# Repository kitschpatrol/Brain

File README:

THIS IS THE SOFTWARE SERIAL BRANCH
==================================
Note, this branch is intended for use with the NewSoftSerial library. (The core SoftwareSerial library doesn't cut it, because it's missing certain function calls.)

Grab and install the NewSoftSerial library here: http://arduiniana.org/libraries/NewSoftSerial/

Eventually, changes to the Arduino core should eliminate the need for separate branches. (e.g. there should be a generic "Serial" object from which both the hardware and software varieties can inherit.)

If you want to use your hardware serial pins (0 and 1, usually), then use the Master branch of this library instead.

LIBRARY OVERVIEW
================
Brain is an Arduino Library for parsing data from Neurosky-based EEG headsets. Tested units include the Star Wars Force Trainer and Mattel MindFlex.

It's designed to make it simple to send out an ASCII string of comma-separated values over serial, or to access processed brain wave information directly in your Arduino sketch. See the examples for code demonstrating each use case.

Instructions for the hardware-end of this hack are available here: http://ericmika.com/itp/brain-hack

The .getCSV() function returns a string (well, char*) listing the most recent brain data, in the following format:
"signal strength, attention, meditation, delta, theta, low alpha, high alpha, low beta, high beta, low gamma, high gamma"

Signal strength ranges from 0 - 200. Counterintuitively, 0 means the unit has connected successfully, and 200 means there is no signal.

The attention and meditation values both run from 0 - 100. Intuitively, higher numbers represent more attention or meditation.

The EEG power values — delta, theta, etc... - are a heavily filtered representation of the relative activity in different brain wavelengths. These values can not be mapped directly to physical values (e.g. volts), but are still of use when considered over time or relative to each other.

INSTALLATION
============
Decompress the zip and drag "Brain" folder to Arduino's "libraries" folder inside your sketch folder. (On the Mac, this is ~/Documents/Arduino by default. You may need to create this folder if it does not exist.) Restart the Arduino environment.

FUNCTION OVERVIEW
=================
Brain(HardwareSerial &_brainSerial) // Instantiates the brain library on a hardware serial port.

boolean update();          // Call this in your main loop to read data from the headset. Returns true if there is a 
fresh packet.

char* readErrors();          // Character string containing the most recent errors. Worth printing this out over serial 
if you're having trouble.

char* readCSV();          // Character string with all of the latest brain values in a comma-delimited format. Intended 
to be printed over serial. The data is in this order: "signal strength, attention, meditation, delta, theta, low alpha, 
high alpha, low beta, high beta, low gamma, high gamma"

byte readSignalQuality();        // Returns the latest signal quality reading. 200 is high, 0 is no signal. This (and 
the remainder of the functions) are mainly intended for use when you want the Arduino to use the brain data internally. 
(Saves you the hassle / memory expenditure of parsing the CSV.)

byte readAttention();        // Returns the NeuroSky "eSense" attention value.

byte readMeditation();        // Returns the NeuroSky "eSense" meditation value.

unsigned long* readPowerArray();  // Returns an array of the eight power-band (FFT) values, in the same order as the 
CSV.

unsigned long readDelta();      // Returns the delta (1-3Hz) power value, often associated with sleep.

unsigned long readTheta();      // Returns the theta (4-7Hz) power value, associated with a relaxed, meditative state.

unsigned long readLowAlpha();    // Returns the low alpha (8-9Hz) power value, higher when eyes are closed or you're 
relaxed/

unsigned long readHighAlpha();    // Returns the high alpha (10-12Hz) power value.

unsigned long readLowBeta();     // Retursn the low beta (13-17Hz) power value, higher when you're alert and focused.

unsigned long readHighBeta();    // Returns the high beta (18-30Hz) power value.

unsigned long readLowGamma();    // Returns the low gamma (31-40Hz) power value, associated with multi-sensory 
processing.

unsigned long readMidGamma();    // Returns the high gamma (41-50Hz) power value.

MINUTIAE
========
Note that the connection to the Neurosky headset is half-duplex — it will use up the RX pin on your Arduino, but you will still be able to send data back to a PC via USB. (Although in this case you won't be able to send data to the Arduino from the PC.)

You may wish to read brain data over a software serial connection instead of the Arduino's hardware serial (this frees up the hardware serial for full-duplex operation). I've tested the library with the Software Serial library distributed with the Arduino environment, and also with the excellent NewSoftSerial library (http://arduiniana.org/libraries/NewSoftSerial), it works fine with both. HOWEVER, switching from the default hardware serial to software serial requires modification of the brain library. I'm looking for a more flexible solution, but for now feel free to contact me if you need help reconfiguring the library to work with software serial.

The MindFlex provides access to more brain data than the Force Trainer — in addition to the signal strength, attention and meditation values, the MindFlex gives access to 8 bands of EEG power data.

Brain data comes in quite slowly... expect a fresh packet every second or so.

CONTACT
========
Eric Mika
ermika@gmail.com
http://ericmika.com/itp

COLOPHON
========
Created by Eric Mika at NYU ITP in the spring of 2010.

My thanks to Tom Igoe for his assistance during development. Thanks also to my collaborators Sofy Yuditskaya and Arturo Vidich.

LICENSE
=======
Copyright Eric Mika, 2010
Licensed under the GNU Lesser General Public License.

This program is free software: you can redistribute it and/or modify it under the terms of the GNU Lesser General Public License as published by the Free Software Foundation, either version 3 of the License, or (at your option) any later version.

This program is distributed in the hope that it will be useful, but WITHOUT ANY WARRANTY; without even the implied warranty of MERCHANTABILITY or FITNESS FOR A PARTICULAR PURPOSE. See the GNU General Public License for more details.

You should have received a copy of the GNU Lesser General Public License along with this program. If not, see http://www.gnu.org/licenses/.

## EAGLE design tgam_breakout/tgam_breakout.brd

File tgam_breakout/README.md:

TGAM Breakout
=============

For Neurosky ThinkGear ASIC Module. breaks out the 2.0mm pitch pins from the
TGAM board to coax and 2.54mm pitch connectors. Has electrode pads too.

Seeed did produce a batch of these for me, they did ask me to doublecheck since this does not pass the DRU but the result was fine. Remember to order in ENIG finish.

## BOM

  - 1 TGAM: http://www.seeedstudio.com/depot/thinkgear-am-brainwave-sensor-p-1441.html?cPath=25_29
  - 1 6 contact pin header 2.0mm: http://www.digikey.fi/product-detail/en/M22-2020305/952-2133-ND/3728097
  - 1 5 contact pin header 2.0mm: http://www.digikey.fi/product-detail/en/M22-2010505/952-2276-ND/3728240
  - 3 UMC cables: http://www.digikey.fi/product-detail/en/2015357-4/A36229-ND/1249193
  - 6 UMC connectors: http://www.digikey.fi/product-detail/en/0734120114/WM3894CT-ND/2421931

Instead of the expensive coax cable and connectors you can use shielded
audio cable and solder that directly on the board, the signal wire goes
on the coax middle (the trace is easy to identify) and shield goes to
either of the two pads of the coax connector shields.

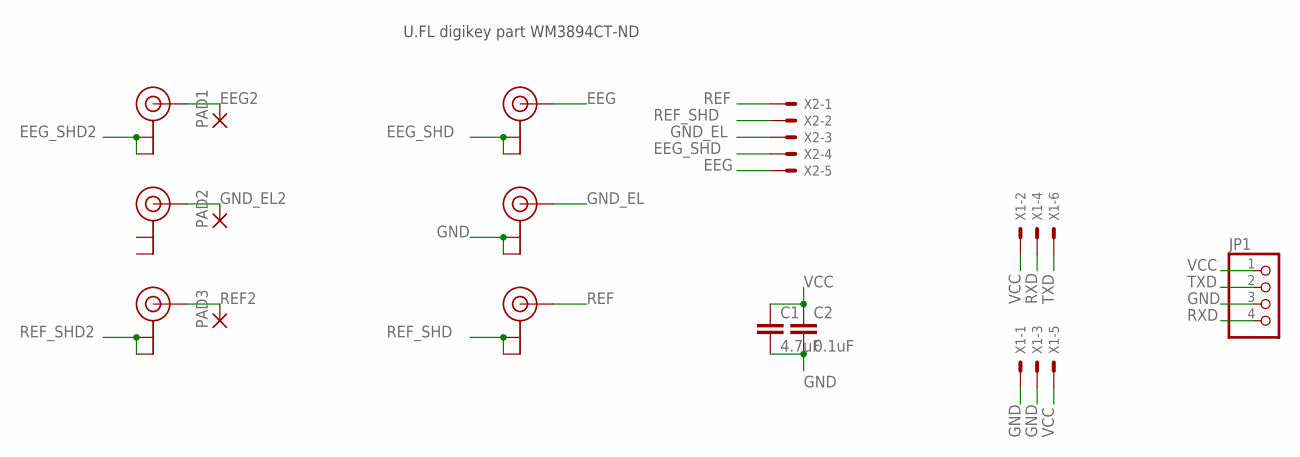
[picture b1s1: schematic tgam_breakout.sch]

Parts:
C1: 4.7uF; C0805
C2: 0.1uF; C0805
EEG: U.FL
EEG_EL: U.FL
GND_EL: U.FL
GND_ELEL: U.FL
JP1: PINHD-1X4; 1X04
PAD1, PAD2, PAD3: SMD5; SMD2,54-5,08
REF: U.FL
REF_EL: U.FL
X1: 332-06
X2: 332-10; 2MM5SIL

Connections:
EEG: EEG.P$3 (SIGNAL), X2.9
EEG2: EEG_EL.P$3 (SIGNAL), PAD1.1
EEG_SHD: EEG.P$1 (GND), EEG.P$2 (GND), X2.7
EEG_SHD2: EEG_EL.P$1 (GND), EEG_EL.P$2 (GND)
GND: C1.2, C2.2, GND_EL.P$1 (GND), GND_EL.P$2 (GND), JP1.3, X1.1, X1.3
GND_EL: GND_EL.P$3 (SIGNAL), X2.5
GND_EL2: GND_ELEL.P$3 (SIGNAL), PAD2.1
REF: REF.P$3 (SIGNAL), X2.1
REF2: PAD3.1, REF_EL.P$3 (SIGNAL)
REF_SHD: REF.P$1 (GND), REF.P$2 (GND), X2.3
REF_SHD2: REF_EL.P$1 (GND), REF_EL.P$2 (GND)
RXD: JP1.4, X1.4
TXD: JP1.2, X1.6
VCC: C1.1, C2.1, JP1.1, X1.2, X1.5

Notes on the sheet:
U.FL digikey part WM3894CT-ND

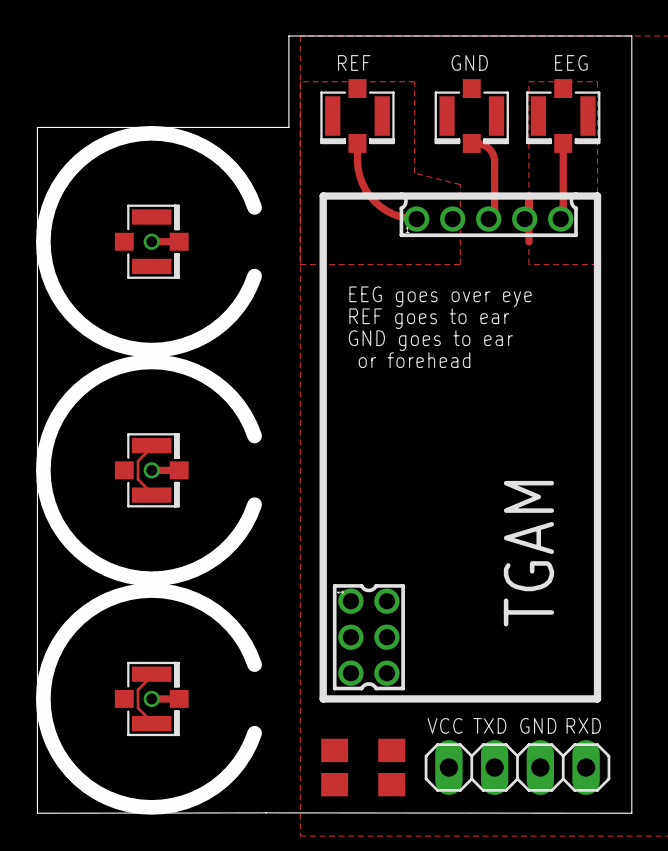
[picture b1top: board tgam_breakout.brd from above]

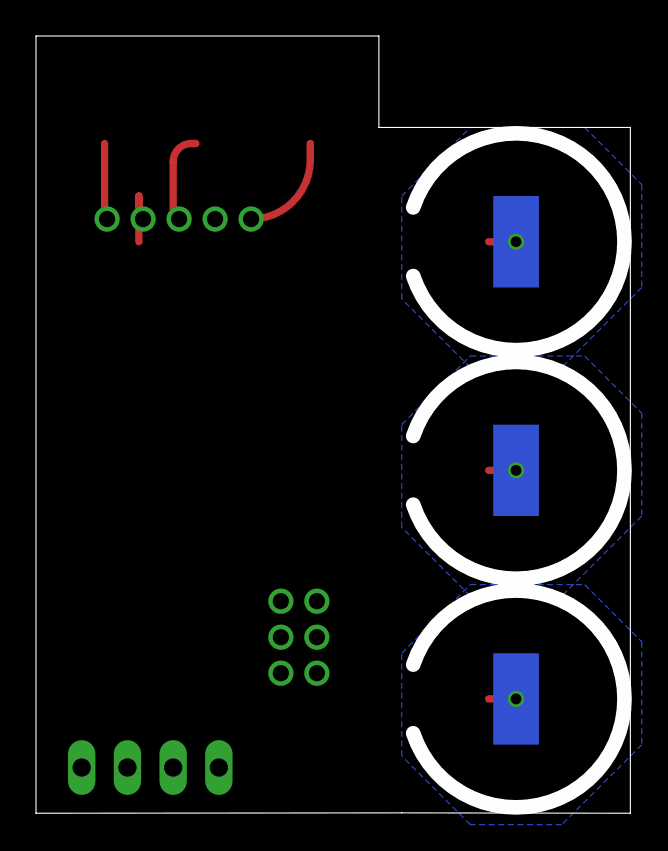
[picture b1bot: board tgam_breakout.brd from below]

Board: 2 copper layers, 32.3 x 42.4 mm, 14 parts (3 on the bottom side), 14 nets.

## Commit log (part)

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2010-02-26 Initial project commit
2010-02-26 Housekeeping... added TextMate project.
2010-02-26 Major rework into half-duplex hardware serial approach. Moved EEG power bands into an array for convenience. Added getters and setters.
2010-02-27 Major rework from broadcast approach to call-response approach. All serial output is now up to the user, the library only cares about the input half of the serial object it's passed.
2010-02-28 Formatting clean up.
2010-02-28 Added string-based error handling and keywords.txt
2010-02-28 Refined examples. Expanded Readme.
2010-03-02 fixed a misspelling
2010-03-02 Added license, changed getter names
2010-04-13 fixed keywords
2010-04-13 added software serial support
2010-04-13 removed some extraneous garbage from the test example
2010-04-13 fixed url in readme
2010-04-13 really fixed url in readme
2010-04-14 added function definitions to the readme
2011-11-13 added some comments clarifying the correspondence to documented hex codes and a TODO about supporting the raw EEG data
2011-11-15 added support for reading the raw values and the update method now returns a bitmark indicating which data is available
2011-11-15 fixed a bug in my raw packet parsing, minor optimizations, made printPacket public since I needed it
2011-12-17 Compatibility with Arduino 1.0
2011-12-17 Arduino 1.0 Compatibility
2012-01-21 rename & fix files for arduino 1.0
2012-01-23 scripted typo fix
2012-01-24 scripted arduino 1.0 changes (use standard C type names)
2012-08-13 switch to flash strings: gsed -i -r -e "s%Serial.print(ln)?\\((\".*?\")\\)%Serial.print\1(F(\2))%g"
2012-11-20 fix a typo caused by previous scripted changes
2012-11-20 added some notes
2013-05-29 drawings for a breakout board
2013-05-29 reorg and readme
2013-06-06 Reformat readme with markdown. Update example file extensions for Arduino 1.0.
2013-06-25 it seems using the flash macro helper here causes compile errors
2013-06-29 seems some inconsistencies were left over
2013-06-29 Oh fsck! I had switched reference electrode and shield connections...
2014-01-15 Compiling again. Adding gitignore for mac cruft.
2014-01-15 Unified Stream-based implementation for hardware and software serial communication.
2014-01-15 Rename examples... add software serial example.
2014-01-15 Readme fixes.
2014-01-15 Update readme with info about software serial support in master.
2014-01-15 Fixed size integers for portability.
2014-01-15 Purge "serial" from variable names in favor of "stream".
2014-01-18 Formatting clean up, back to simpler boolean update() return value.
2014-01-18 Mention examples in readme.
2014-01-18 Change folder structure for easy "Add Library..." installation through the Arduino IDE.
2014-01-18 Add repo rename to Readme, add new zip installation instructions.
2014-01-18 Fix compile error.
2014-01-19 Readme updates in preparation for 1.0 release.
2015-04-20 Update readme.
2017-02-26 Strip trailing whitespace from source code files
2017-02-26 Replace stray tabs with spaces
2017-03-29 Fix Markdown header rendering
    GitHub recently updated their Markdown renderer to require a space
    between the `#` characters and the title of a header. See here for
    details: https://github.com/github/markup/issues/1013
    This change was made by running:
    sed --in-place 's/^\(##*\)\([^# ]\)/\1 \2/' README.md
2019-12-01 Fix warnings
    The construction
    a = b[++i] << 8 | c[++i];
    has an undefined result. The compiler is free to reorder the
    pre-increment however it sees fit.
    Fix by making the order explicit
    Also remove unused variable that emitted a warning.
2021-11-23 adding draft serial program
2021-11-23 fixes
2023-11-19 Update readme, clarify readSignalQuality values.
2023-11-23 Clarify device compatibility in readme.
2024-06-19 Fix typo in readme.

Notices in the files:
parts and their libraries:
SparkFun-Connectors: Licensing: CC v3.0 Share-Alike You are welcome to use this library for commercial purposes.
